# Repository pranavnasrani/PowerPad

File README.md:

# PowerPad

Hello! Welcome to my PowerPad GitHub repository!
You will find all the details for my HackPad in this repository

## Render of the MacroPad

## Inspiration and Ideation

I use my computer a lot, especially for video editing, and a lot of coding/multitasking. I wanted to make a MacroPad that makes my life easier, helps me copy, paste, cut, undo, redo, all with ease. I use these shortcuts atleast 40 times a day, and having them just a buttons press away would be amazing. I also added a Rotary Encoder to control my volume (for my music), and possibly in the future, to scrub the video editing timeline. The OLED screen would display the current time and some cool graphics (have to work on that in the future through client based code). 

## Challenges
This was not my first time using Fusion, however it was my first time doing PCB design, and I ran into a lot of problems with the footprints, and how to set up vias, but now I can confidently design simple PCBs.
## Specs
**Bill of Materials**

 - 6x Cherry MX Switches
 - 1x XIAO RP2040
 - 6x Blank DSA Keycaps (white)
-  1x 0.91 inch OLED display
-  1x EC11 Rotary Encoder
-  4x M3x16mm screws
-  4x M3x5mx4mm heatset inserts
## PCB

## Schematic

## Case

Case files (top and bottom case STEP files) can be found [here](https://github.com/pranavnasrani/PowerPad/tree/master/cad/case%20files)

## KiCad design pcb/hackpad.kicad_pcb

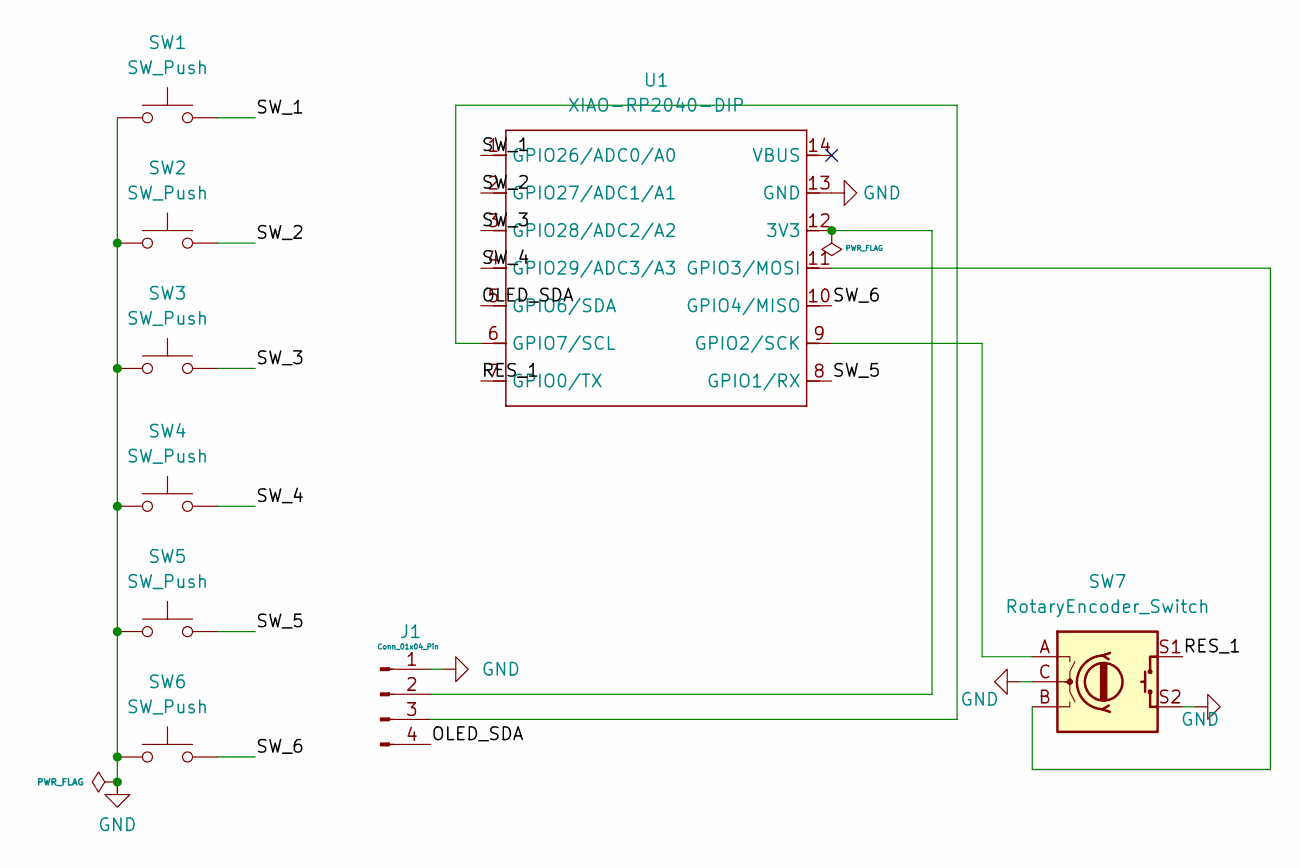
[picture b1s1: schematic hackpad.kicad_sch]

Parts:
J1: Conn_01x04_Pin; PinHeader_1x04_P2.54mm_Vertical
SW1, SW2, SW3, SW4, SW5, SW6: SW_Push; SW_Cherry_MX_1.00u_PCB
SW7: RotaryEncoder_Switch; RotaryEncoder_Alps_EC11E-Switch_Vertical_H20mm
U1: XIAO-RP2040-DIP

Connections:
/OLED_SDA: J1.4, U1.5 (GPIO6/SDA)
/RES_1: SW7.S1, U1.7 (GPIO0/TX)
/SW_1: SW1.2, U1.1 (GPIO26/ADC0/A0)
/SW_2: SW2.2, U1.2 (GPIO27/ADC1/A1)
/SW_3: SW3.2, U1.3 (GPIO28/ADC2/A2)
/SW_4: SW4.2, U1.4 (GPIO29/ADC3/A3)
/SW_5: SW5.2, U1.8 (GPIO1/RX)
/SW_6: SW6.2, U1.10 (GPIO4/MISO)
GND: J1.1, SW1.1, SW2.1, SW3.1, SW4.1, SW5.1, SW6.1, SW7.C, SW7.S2, U1.13 (GND)
unnamed: J1.2, U1.12 (3V3)
unnamed: J1.3, U1.6 (GPIO7/SCL)
unnamed: SW7.A, U1.9 (GPIO2/SCK)
unnamed: SW7.B, U1.11 (GPIO3/MOSI)

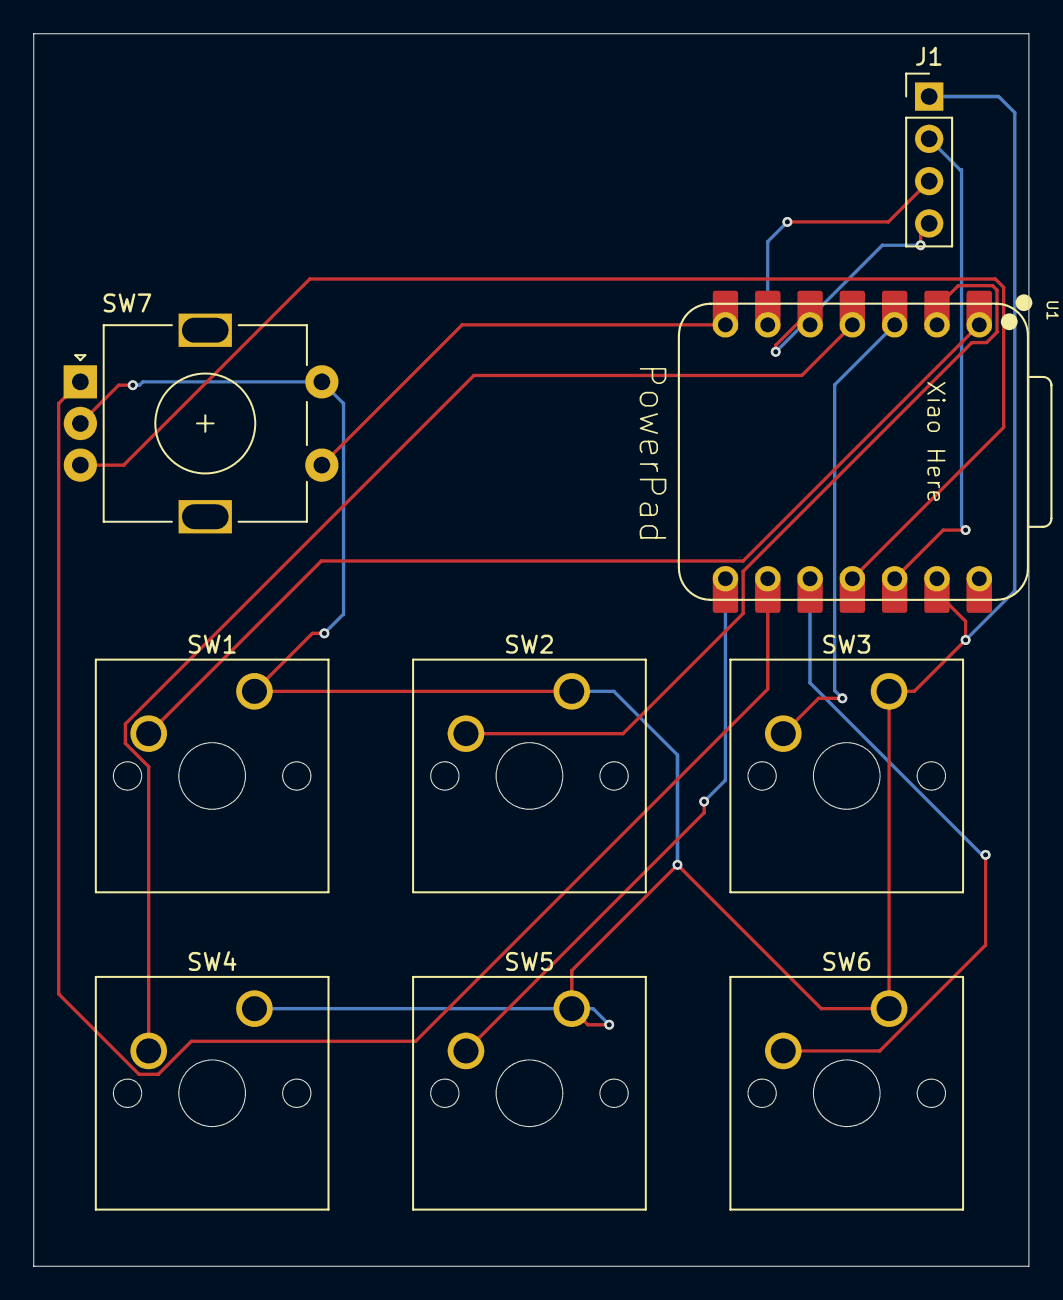
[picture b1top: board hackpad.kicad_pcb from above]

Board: 2 copper layers, 59.8 x 74.0 mm, 9 parts (0 on the bottom side), 13 nets.

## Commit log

2026-01-12 first commit for my powerpad
2026-01-12 Initialize README with project details and images
    Added detailed project description, specs, and images.
2026-01-13 added case cad files after design review
2026-01-13 Add link to case files in README
    Added link to case files for the project.
